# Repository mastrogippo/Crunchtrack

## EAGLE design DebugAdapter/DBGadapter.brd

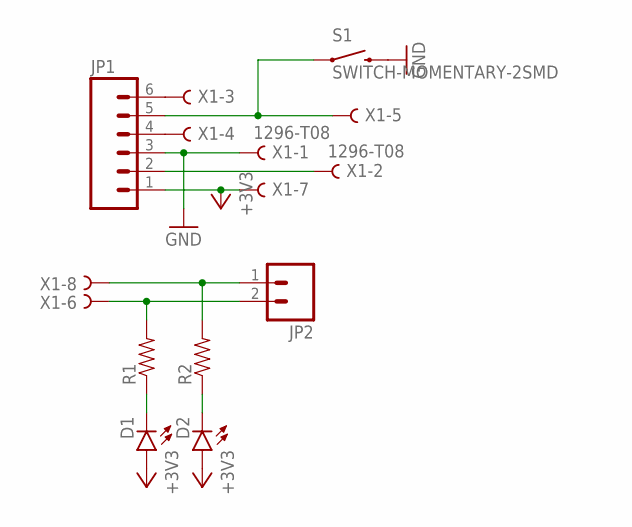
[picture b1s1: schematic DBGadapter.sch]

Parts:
D1, D2: LED0603; LED-0603
JP1: M06LOCK_LONGPADS; 1X06_LOCK_LONGPADS
JP2: M02LOCK_LONGPADS; 1X02_LOCK_LONGPADS
R1, R2: RESISTOR0805-RES; 0805
S1: SWITCH-MOMENTARY-2SMD; TACTILE-SWITCH-SMD
X1: 1296-T08; 1296-08

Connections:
+3V3: D1.A, D2.A, JP1.1, X1.7
GND: JP1.3, S1.3 (2), X1.1
unnamed: JP1.2, X1.2
unnamed: JP1.4, X1.4
unnamed: JP1.5, S1.1, X1.5
unnamed: JP1.6, X1.3
unnamed: JP2.1, R2.2, X1.8
unnamed: JP2.2, R1.2, X1.6
unnamed: D2.C, R2.1
unnamed: D1.C, R1.1

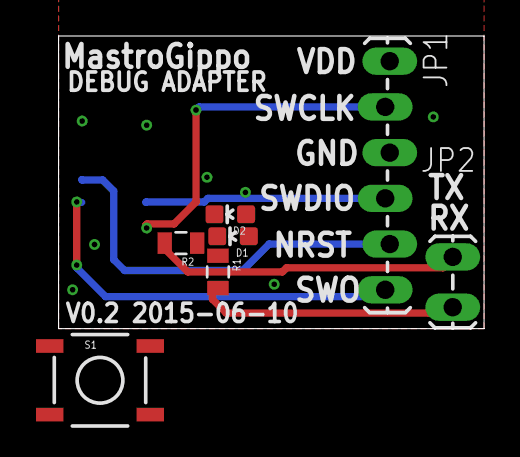
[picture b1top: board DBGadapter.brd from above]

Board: 2 copper layers, 23.6 x 16.3 mm, 8 parts (1 on the bottom side), 10 nets.

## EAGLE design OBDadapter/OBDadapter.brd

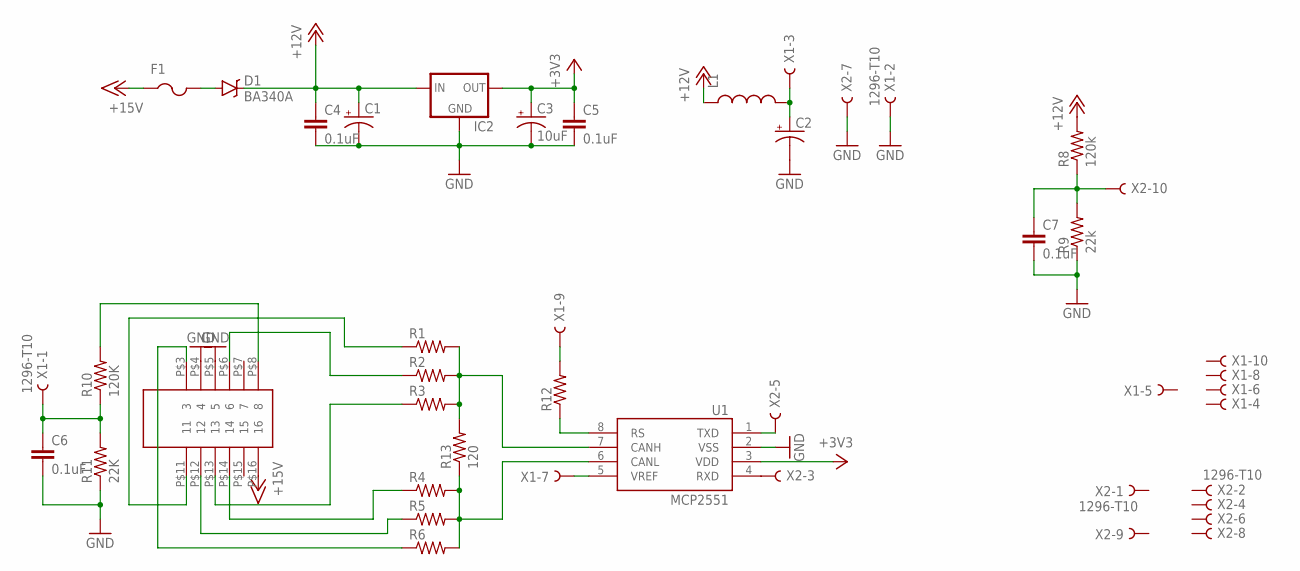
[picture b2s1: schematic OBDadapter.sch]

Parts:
C1: CAP_POL3528-KIT; EIA3528-KIT
C2: CAP_POL6032; EIA6032
C3: 10uF; EIA3528
C4, C5, C6, C7: 0.1uF; 0603-CAP
D1: BA340A; SMA-DIODE
F1: PTCFUSE-1206; R1206
IC2: V_REG_78XXSOT89; SOT89
L1: INDUCTOR1210; 1210
R1, R2, R3, R4, R5, R6, R12: RESISTOR0805-RES; 0805
R8: 120k; 0805
R9: 22k; 0805
R10: 120K; 0805
R11: 22K; 0805
R13: 120; 0805
U1: MCP2551; SO08
U$1: OBD-4
X1, X2: 1296-T10; 1296-10

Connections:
+3V3: C3.A (+), C5.1, IC2.1 (OUT), U1.3 (VDD)
+12V: C1.A (+), C4.1, D1.C, IC2.3 (IN), L1.1, R8.2
+15V: F1.1, U$1.P$16 (16)
GND: C1.C (-), C2.P$2 (-), C3.C (-), C4.2, C5.2, C6.2, C7.2, IC2.2 (GND), IC2.4 (GND), R9.1, R11.1, U1.2 (VSS), U$1.P$4 (4), U$1.P$5 (5), X1.2, X2.7
unnamed: R1.1, U$1.P$11 (11)
unnamed: R2.1, U$1.P$6 (6)
unnamed: R5.1, U$1.P$12 (12)
unnamed: R3.1, U$1.P$13 (13)
unnamed: R4.1, U$1.P$14 (14)
unnamed: R1.2, R2.2, R3.2, R13.2, U1.7 (CANH)
unnamed: R6.1, U$1.P$3 (3)
unnamed: U1.1 (TXD), X2.5
unnamed: U1.4 (RXD), X2.3
unnamed: R12.2, X1.9
unnamed: U1.5 (VREF), X1.7
unnamed: R4.2, R5.2, R6.2, R13.1, U1.6 (CANL)
unnamed: D1.A, F1.2
unnamed: R10.2, U$1.P$8 (8)
unnamed: C7.1, R8.1, R9.2, X2.10
unnamed: C6.1, R10.1, R11.2, X1.1
unnamed: R12.1, U1.8 (RS)
unnamed: C2.P$1 (+), L1.2, X1.3

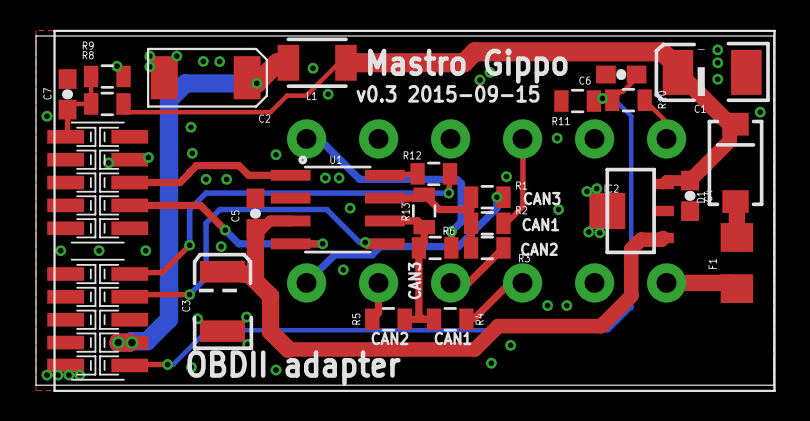
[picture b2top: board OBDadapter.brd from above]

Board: 2 copper layers, 41.0 x 19.4 mm, 28 parts (0 on the bottom side), 22 nets.

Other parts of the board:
U$2: OSHWLOGO_TOL_0.2

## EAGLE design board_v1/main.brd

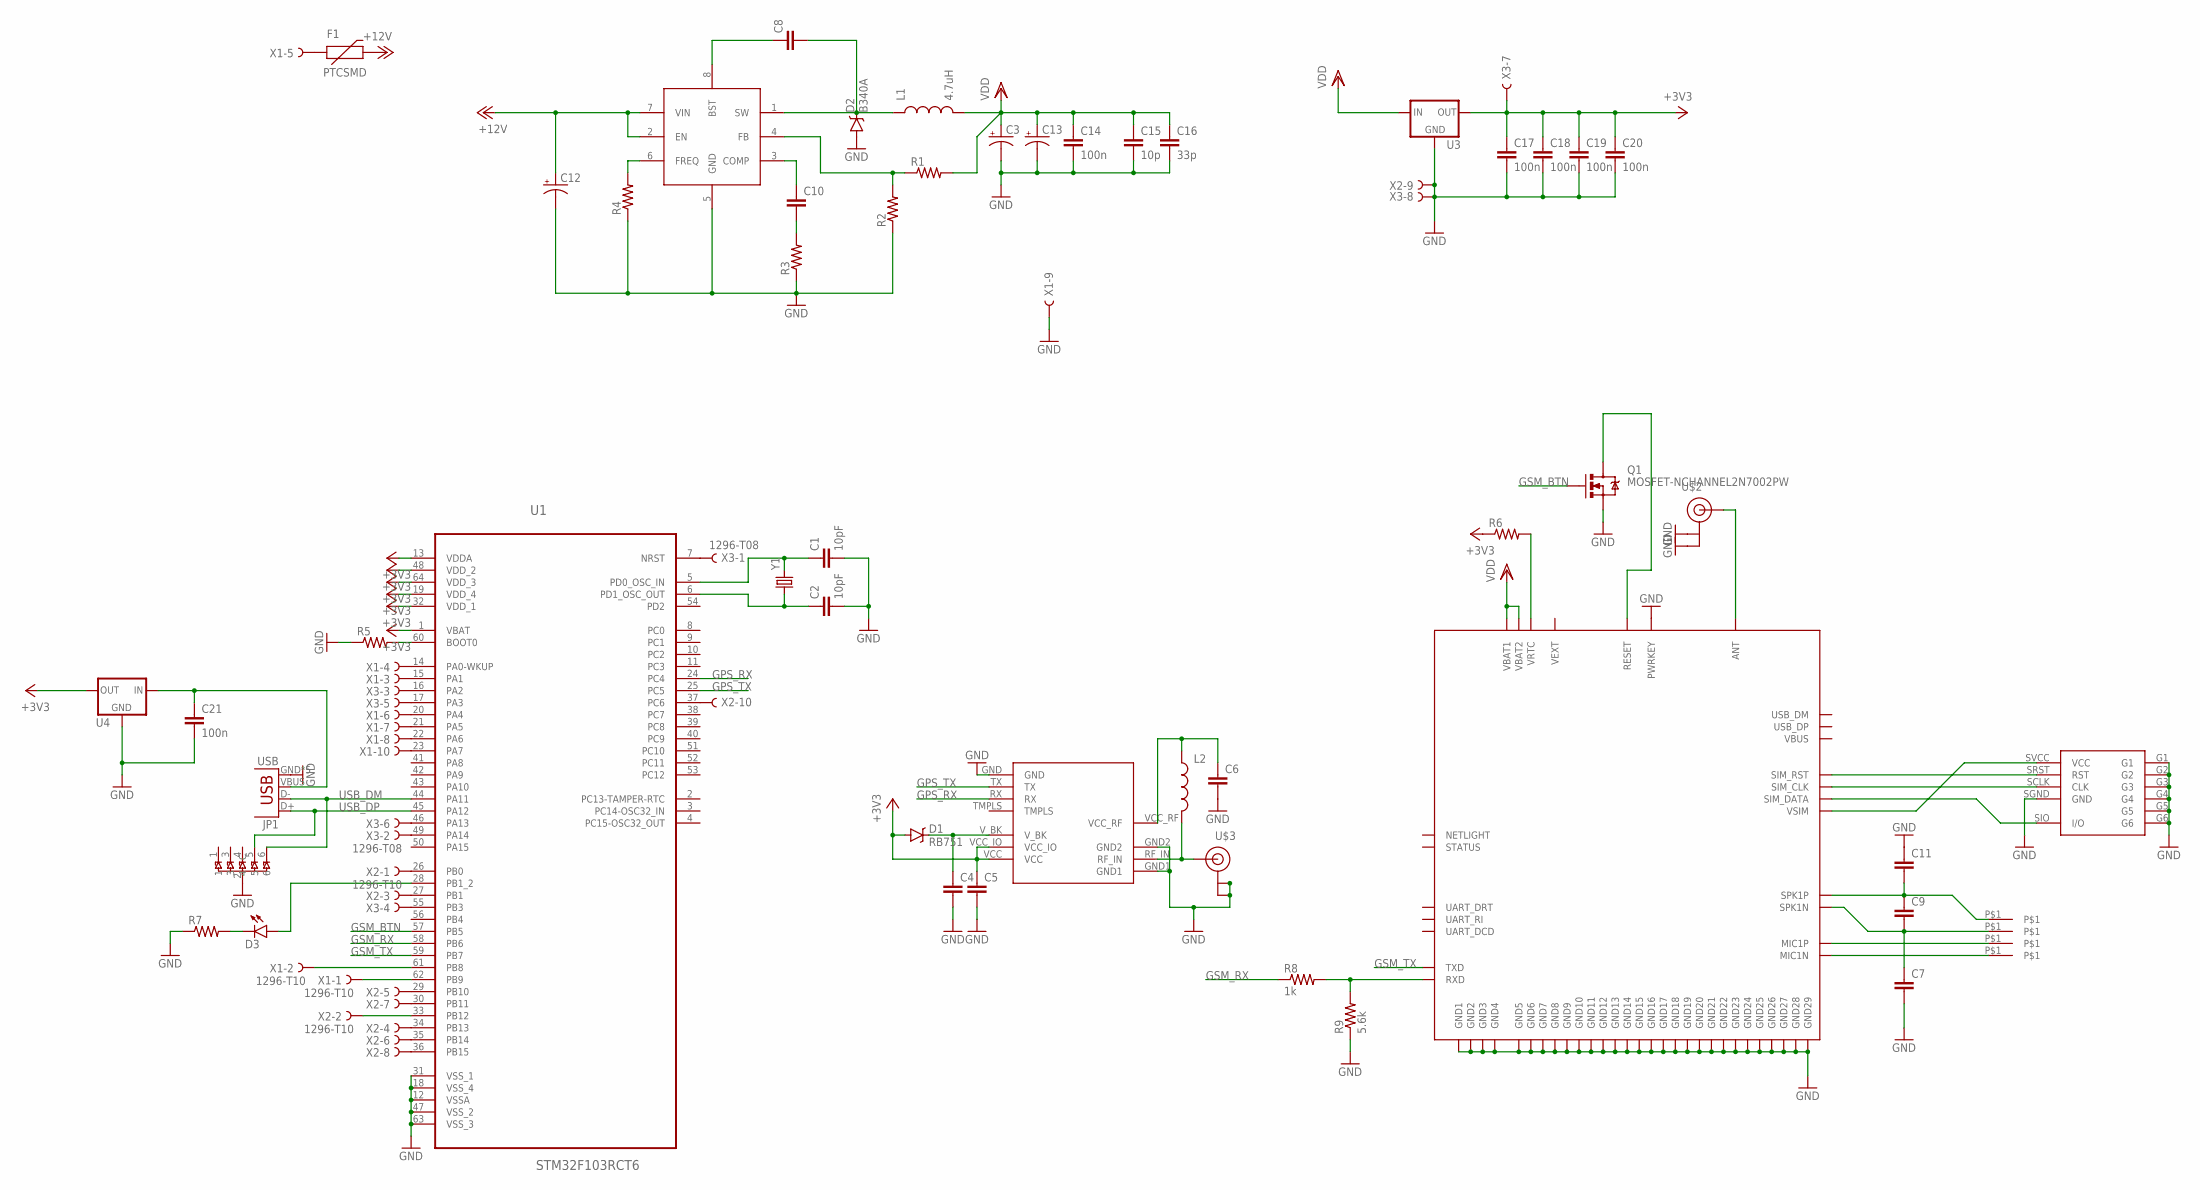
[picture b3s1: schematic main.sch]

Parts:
C1, C2: 10pF; 0603-CAP
C3, C13: CAP_POL6032; EIA6032
C4, C5: CAP1210; 1210
C6, C7, C9, C10, C11: CAP0402-CAP; 0402-CAP
C8: CAP0805; 0805
C12: CPOL-USSMCC; SMC_C
C14, C17, C18, C19, C20, C21: 100n; 0805
C15: 10p; 0402-CAP
C16: 33p; 0402-CAP
D1: RB751; SOD-523
D2: B340A; SMA-DIODE
D3: LED0603; LED-0603
F1: PTCSMD; PTC-1206
JP1: USB; USB-MICROB-2
L1: 4.7uH; CR75
L2: INDUCTOR0402; C0402
Q1: MOSFET-NCHANNEL2N7002PW; SOT323
R1, R2, R3, R4, R5, R6, R7: RESISTOR0402-RES; 0402-RES
R8: 1k; 0402-RES
R9: 5.6k; 0402-RES
U1: STM32F103RCT6; QFP50P1200X1200X160-64N
U2: MP1584; SO8
U3, U4: XC63FPM; SOT23
U5: SMF05C; SC70-6L
U$1: SIM800_MIN
U$2, U$3: U.FL; U.FL2
U$4: VK_GPS_U7_MIN
U$7: SIM_NOVPP; WURTH_NANO_SIM_NOVPP
U$8, U$9, U$13, U$14: PAD1
X1, X2: 1296-T10; 1296-10
X3: 1296-T08; 1296-08
Y1: CRYSTAL5X3; CRYSTAL-SMD-5X3

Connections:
+3V3: C5.1, C17.1, C18.1, C19.1, C20.1, D1.A, R6.1, U1.1 (VBAT), U1.13 (VDDA), U1.19 (VDD_4), U1.32 (VDD_1), U1.48 (VDD_2), U1.64 (VDD_3), U3.2 (OUT), U4.2 (OUT), U$4.VCC, U$4.VCC_IO, X3.7
+12V: C12.+, F1.2, U2.2 (EN), U2.7 (VIN)
GND: C1.2, C2.2, C3.P$2 (-), C4.2, C5.2, C6.2, C7.2, C11.1, C12.-, C13.P$2 (-), C14.2, C15.2, C16.2, C17.2, C18.2, C19.2, C20.2, C21.2, D2.A, JP1.GND, JP1.MT1 (GND), JP1.MT2 (GND), JP1.P$1 (GND), JP1.P$2 (GND), Q1.2 (S), R2.1, R3.1, R4.1, R5.1, R7.1, R9.1, U1.12 (VSSA), U1.18 (VSS_4), U1.31 (VSS_1), U1.47 (VSS_2), U1.63 (VSS_3), U2.5 (GND), U3.1 (GND), U4.1 (GND), U5.2 (C), U$1.P$2 (GND1), U$1.P$6 (GND2), U$1.P$8 (GND3), U$1.P$35 (GND29), U$1.P$37 (GND28), U$1.P$38 (GND27), U$1.P$39 (GND26), U$1.P$41 (GND25), U$1.P$43 (GND22), U$1.P$44 (GND23), U$1.P$45 (GND24), U$1.P$48 (PWRKEY), U$1.P$58 (GND4), U$1.P$67 (GND17), U$1.P$71 (GND18), U$1.P$72 (GND19), U$1.P$73 (GND20), U$1.P$76 (GND21), U$1.P$77 (GND5), U$1.P$78 (GND6), U$1.P$79 (GND7), U$1.P$80 (GND8), U$1.P$81 (GND9), U$1.P$82 (GND10), U$1.P$83 (GND11), U$1.P$84 (GND12), U$1.P$85 (GND13), U$1.P$86 (GND14), U$1.P$87 (GND15), U$1.P$88 (GND16), U$2.P$1 (GND), U$2.P$2 (GND), U$3.P$1 (GND), U$3.P$2 (GND), U$4.GND, U$4.GND1, U$4.GND2, U$7.G1, U$7.G2, U$7.G3, U$7.G4, U$7.G5, U$7.G6, U$7.SGND (GND), X1.9, X2.9, X3.8
GPS_RX: U1.24 (PC4), U$4.RX
GPS_TX: U1.25 (PC5), U$4.TX
GSM_BTN: Q1.1 (G), U1.57 (PB5)
GSM_RX: R8.1, U1.58 (PB6)
GSM_TX: U1.59 (PB7), U$1.P$32 (TXD)
unnamed: U$1.P$40 (ANT), U$2.P$3 (SIGNAL)
unnamed: C1.1, U1.5 (PD0_OSC_IN), Y1.3 (2)
unnamed: C2.1, U1.6 (PD1_OSC_OUT), Y1.1
unnamed: U1.16 (PA2), X3.3
unnamed: U1.17 (PA3), X3.5
unnamed: U1.7 (NRST), X3.1
unnamed: U1.55 (PB3), X3.4
unnamed: U1.49 (PA14), X3.2
unnamed: U1.46 (PA13), X3.6
unnamed: C7.1, C9.2, U$1.P$13 (SPK1N), U$9.P$1
unnamed: U$1.P$15 (SIM_RST), U$7.SRST (RST)
unnamed: U$1.P$55 (SIM_CLK), U$7.SCLK (CLK)
unnamed: U$1.P$14 (SIM_DATA), U$7.SIO (I/O)
unnamed: U$1.P$16 (VSIM), U$7.SVCC (VCC)
unnamed: C9.1, C11.2, U$1.P$53 (SPK1P), U$8.P$1
unnamed: U$1.P$52 (MIC1P), U$13.P$1
unnamed: U$1.P$12 (MIC1N), U$14.P$1
unnamed: L2.2, U$3.P$3 (SIGNAL), U$4.RF_IN
unnamed: Q1.3 (D), U$1.P$49 (RESET)
unnamed: U1.61 (PB8), X1.2
unnamed: C4.1, D1.C, U$4.V_BK
unnamed: C6.1, L2.1, U$4.VCC_RF
unnamed: U1.62 (PB9), X1.1
unnamed: C8.1, U2.8 (BST)
unnamed: C8.2, D2.C, L1.P$1 (1), U2.1 (SW)
unnamed: R5.2, U1.60 (BOOT0)
unnamed: C10.1, U2.3 (COMP)
unnamed: C10.2, R3.2
unnamed: R1.1, R2.2, U2.4 (FB)
unnamed: U1.15 (PA1), X1.3
unnamed: U1.14 (PA0-WKUP), X1.4
unnamed: U1.27 (PB1), X2.3
unnamed: U1.20 (PA4), X1.6
unnamed: U1.21 (PA5), X1.7
unnamed: R4.2, U2.6 (FREQ)
unnamed: U1.22 (PA6), X1.8
unnamed: U1.23 (PA7), X1.10
unnamed: U1.26 (PB0), X2.1
unnamed: U1.29 (PB10), X2.5
unnamed: U1.30 (PB11), X2.7
unnamed: U1.33 (PB12), X2.2
unnamed: U1.34 (PB13), X2.4
unnamed: U1.35 (PB14), X2.6
unnamed: U1.36 (PB15), X2.8
unnamed: U1.37 (PC6), X2.10
unnamed: F1.1, X1.5
unnamed: C21.1, JP1.VBUS, U4.3 (IN)
unnamed: R6.2, U$1.P$56 (VRTC)
unnamed: D3.A, U1.28 (PB1_2)
unnamed: D3.C, R7.2
unnamed: R8.2, R9.2, U$1.P$31 (RXD)
USB_DM: JP1.D-, U1.44 (PA11), U5.6
USB_DP: JP1.D+, U1.45 (PA12), U5.5
VDD: C3.P$1 (+), C13.P$1 (+), C14.1, C15.1, C16.1, L1.P$2 (2), R1.2, U3.3 (IN), U$1.P$1 (VBAT1), U$1.P$42 (VBAT2)

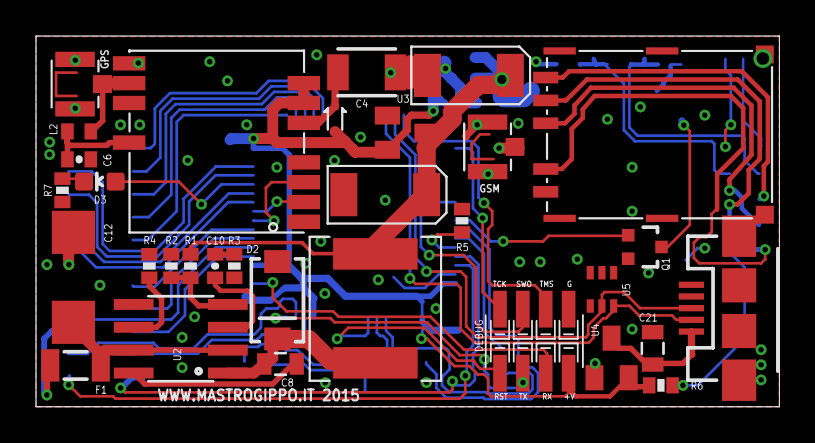
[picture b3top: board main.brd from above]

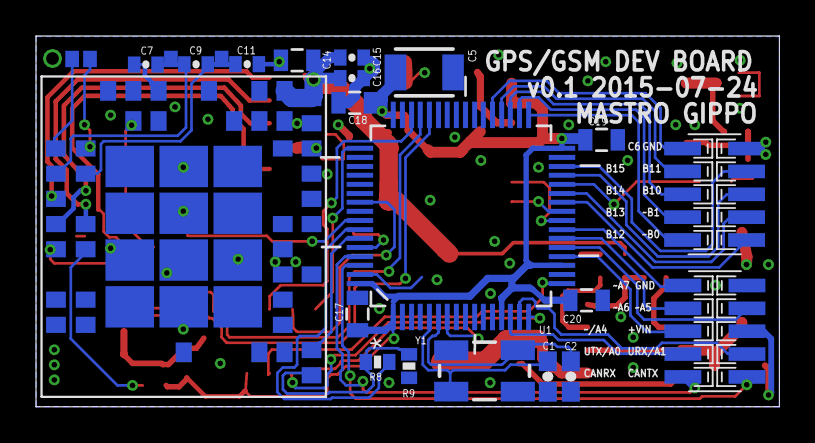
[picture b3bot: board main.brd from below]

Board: 2 copper layers, 41.3 x 20.6 mm, 56 parts (24 on the bottom side), 62 nets.

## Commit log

2015-08-17 :confetti_ball: Added .gitattributes & .gitignore files
2015-08-17 + schematics
2015-09-15 Added OBD adapter
2015-09-19 Added debug adapter board

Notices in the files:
parts and their libraries:
SparkFun-Connectors: Licensing: Creative Commons ShareAlike 4.0 International - https://creativecommons.org/licenses/by-sa/4.0
